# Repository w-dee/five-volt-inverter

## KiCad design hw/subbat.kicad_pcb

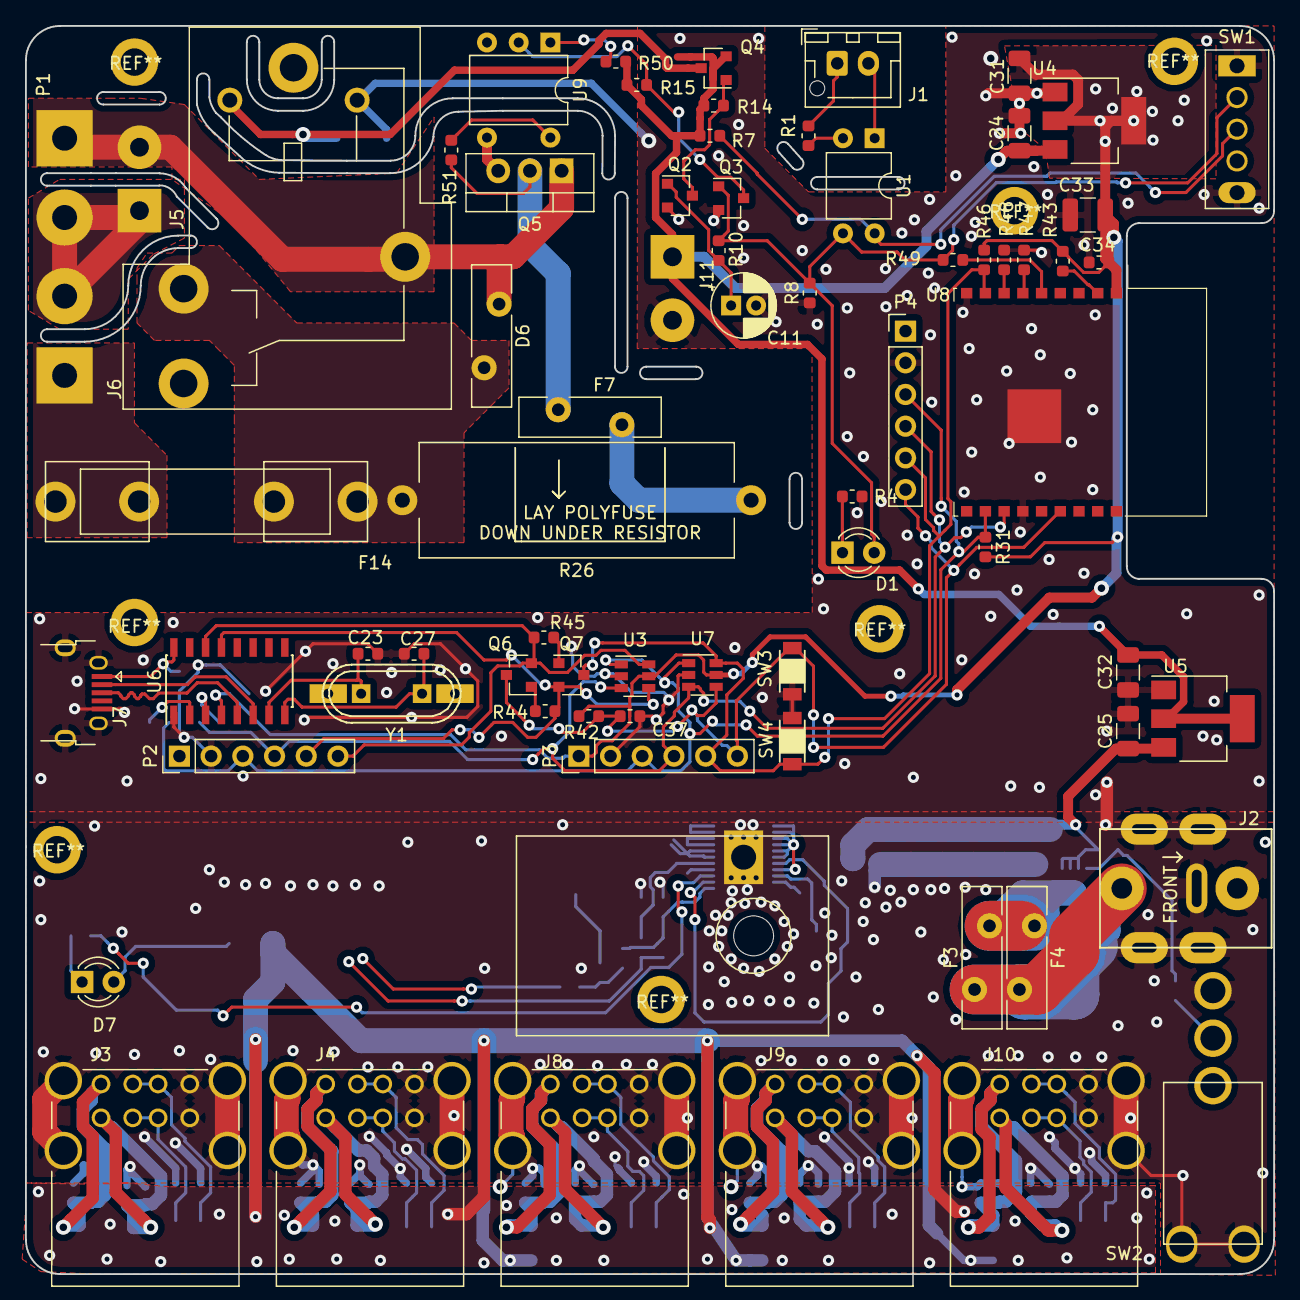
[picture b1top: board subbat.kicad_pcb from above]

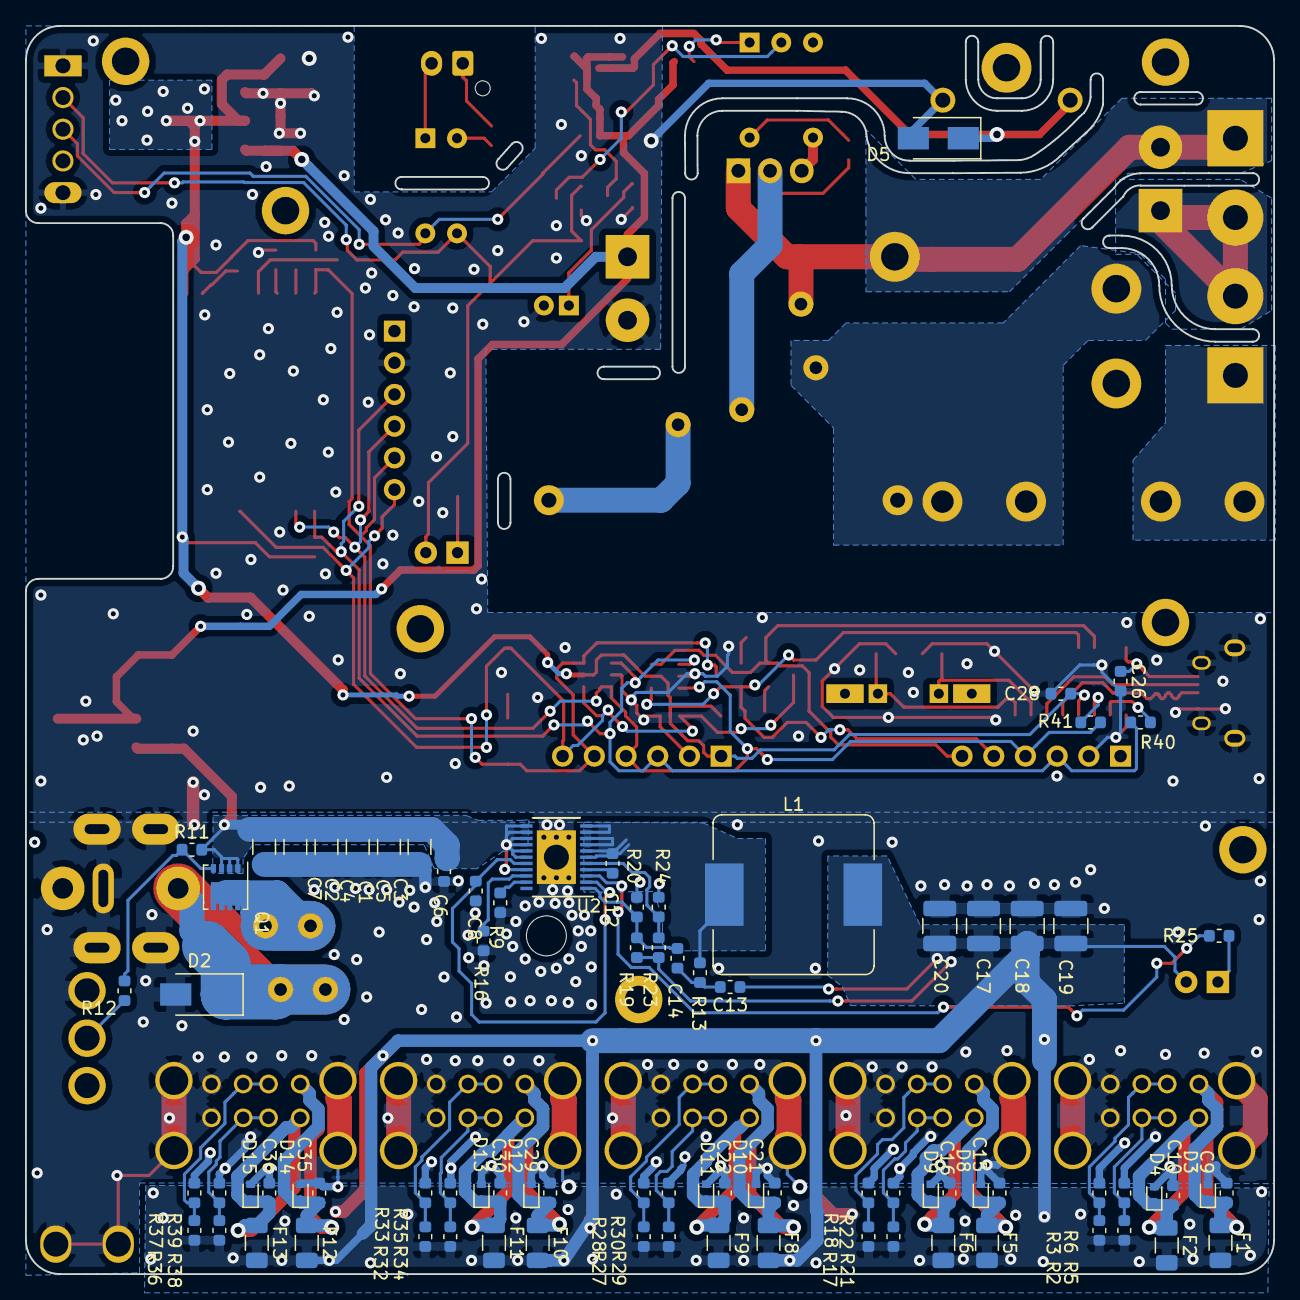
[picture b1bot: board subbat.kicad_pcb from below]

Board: 2 copper layers, 100.0 x 100.0 mm, 155 parts (84 on the bottom side), 77 nets.

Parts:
C1, C2, C3, C4, C5, C7, C24, C25, C31, C32: 10u; C_1206_3216Metric
C6, C8, C9, C10, C15, C16, C21, C22, C26, C28, C29, C30, C34, C35, C36: 1u; C_0603_1608Metric
C11: 22u; CP_Radial_D5.0mm_P2.00mm
C12, C13, C37: 0.1u; C_0603_1608Metric
C14: 1n; C_0603_1608Metric
C17, C18, C19, C20, C33: 100u/6.3V; C_1210_3225Metric
C23, C27: 22p; C_0603_1608Metric
D1, D7: LED; LED_D3.0mm
D2: 28V TVS; D_SMA
D3, D4, D8, D9, D10, D11, D12, D13, D14, D15: 6V; D_SOD-523
D5: D_Schottky_Small; D_SMA
D6: TSV07D271KR; Fuse_Bourns_MF-RG700
F1, F2, F5, F6, F8, F9, F10, F11, F12, F13: 2A; Fuse_1206_3216Metric
F3, F4: 3A hold; Fuse_Bourns_MF-RG700
F7: LVR040S 0.4A hold, 0.9A trip; Fuse_Bourns_MF-RHT600
F14: 15A; FUSE-HOLDER-FUC-03A-20mm_x_5.2mm
J1: Conn_01x02_Female; JST_XH_B02B-XH-AM_1x02_P2.50mm_Vertical
J2: Barrel_Jack; BARREL_JACK_HIGH_CURRENT_PJ018
J3, J4, J8, J9, J10: USB_Ax2
J5, J11: Conn_01x02_Female; SolderWirePad_1x02_P5.08mm_Drill1.5mm
J6: Conn_WallSocket; SolderWirePad_1x02_P7.62mm_Drill2mm
J7: USB_B_Micro; USB_Micro-B_Jing_A01SB141B1-067
K1: 953-1C-5DG-1
L1: 1.5uH 29A; L_Bourns_SRP1245A
P1: Conn_WallPlug; SolderWirePad_1x02_P7.62mm_Drill2mm
P2, P3, P4: CONN_01X06; PinHeader_1x06_P2.54mm_Vertical
Q1: DMP3007SCG; Diodes_PowerDI3333-8
Q2, Q3: 2N7002; SOT-23
Q4: Q_PMOS_GSD; SOT-23
Q5: BTA24-600CW; TO-220-3_Vertical
Q6, Q7: Q_NPN_BEC; SOT-23
R1, R49, R51: 100R; R_0603_1608Metric
R2, R3, R5, R6, R17, R18, R21, R22, R27, R28, R29, R30, R32, R33, R34, R35, R36, R37, R38, R39: DNI; R_0603_1608Metric
R4: 2.2k; R_0603_1608Metric
R7: 10R; R_0603_1608Metric
R8, R15, R20, R24, R31, R43, R44, R45, R47, R48: 10k; R_0603_1608Metric
R9: 150k; R_0603_1608Metric
R10: 22k; R_0603_1608Metric
R11: 1M; R_0603_1608Metric
R12: 22K; R_0603_1608Metric
R13: 3k; R_0603_1608Metric
R14, R42, R46: 100k; R_0603_1608Metric
R16: 200k; R_0603_1608Metric
R19, R23: 75k; R_0603_1608Metric
R25: 1k; R_0603_1608Metric
R26: 100R; R_Axial_Power_L25.0mm_W9.0mm_P27.94mm
R40, R41: 120R; R_0603_1608Metric
R50: 330R; R_0603_1608Metric
SW1: SW_SPDT_WITH_SHIELD; SW_SPDT_WITH_SHILD
SW2: SW_SPDT_WITH_SHIELD; SW_SPDT_v
SW3, SW4: SW_PUSH_SMALL_H; TACT_SW_SMD_Panasonic-EVPAWBD2A
U1: PC817; DIP-4_W7.62mm
U2: TPS53319; DFN-22-1EP_5x6mm_P0.5mm_EP3.14x4.3mm
U3, U7: CM1293A-04SO; SOT-23-6
U4: AZ1117-3.3; SOT-223-3_TabPin2
U5: AZ1117-5.0; SOT-223-3_TabPin2
U6: CH340G; SOIC-16_3.9x9.9mm_P1.27mm
U8: ESP-WROOM-02
U9: TLP561J; Toshiba_11-7A9
Y1: Crystal; Crystal_HC49-U_Vertical_SMD_Universal

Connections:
+3V3: C28.1, C31.1, C33.1, C34.1, P3.1, R31.2, R42.1, R43.1, R46.1, U3.5, U4.2, U6.4, U7.5, U8.1
+5V: C24.1, C32.1, J11.1, Q4.2, R7.2, R14.1, R15.1, R50.2, U4.3, U5.2
/AC_IN_L: D6.1, J5.2, K1.5, P1.1, Q5.1
/AC_IN_N: J5.1, J6.2, P1.2
/AC_OUT_L: D6.2, F14.1, K1.1, R26.2
/AC_OUT_L_2: F14.2, J6.1
/LL: C12.2, L1.1, R13.1, U2.6, U2.7, U2.8, U2.9, U2.10, U2.11
/SW: D1.2, Q3.1, R8.2, R10.2, R49.2, SW1.1, U1.3
/VIN: C1.1, C2.1, C3.1, C4.1, C5.1, C6.1, C7.1, C25.1, Q1.1, Q1.2, Q1.3, R11.2, U2.12, U2.13, U2.14, U2.15, U2.16, U2.17, U2.19, U5.3
DTR: P2.5, Q7.2, R44.2, U3.4, U6.13
E_EN: C37.2, P3.6, P4.6, Q6.3, R42.2, SW3.1, U7.4, U8.15
E_GPIO0: P3.5, P4.5, Q7.3, R46.2, SW4.2, U7.6, U8.8
E_RX: P2.3, P3.3, P4.3, R31.1, R40.2, U3.1, U7.1, U8.11
E_TX: P2.4, P3.4, P4.4, R41.2, U3.3, U7.3, U8.12
GND: C1.2, C2.2, C3.2, C4.2, C5.2, C6.2, C7.2, C8.2, C9.2, C10.2, C11.2, C15.2, C16.2, C17.2, C18.2, C19.2, C20.2, C21.2, C22.2, C23.2, C24.2, C25.2, C26.2, C27.2, C28.2, C29.2, C30.2, C31.2, C32.2, C33.2, C34.2, C35.2, C36.2, C37.1, D2.2, D3.2, D4.2, D5.2, D8.2, D9.2, D10.2, D11.2, D12.2, D13.2, D14.2, D15.2, J2.2, J2.3, J3.4, J3.8, J3.9, J4.4, J4.8, J4.9, J7.5, J7.6, J8.4, J8.8, J8.9, J9.4, J9.8, J9.9, J10.4, J10.8, J10.9, J11.2, K1.3, P2.2, P3.2, P4.2, Q2.2, Q3.2, R3.2, R4.1, R6.2, R8.1, R9.1, R16.2, R18.2, R20.2, R22.2, R24.2, R28.2, R30.2, R33.2, R35.2, R37.2, R39.2, R47.2, R48.2, SW1.4, SW1.5, SW2.3, SW2.4, SW2.5, SW3.2, SW4.1, U2.23, U3.2, U4.1, U5.1, U6.1, U7.2, U8.9, U8.13, U8.18, U8.19
unnamed: C8.1, U2.2, U2.18
unnamed: C9.1, D3.1, F1.1, J3.1
unnamed: C10.1, D4.1, F2.1, J3.5
unnamed: C11.1, Q2.1, R10.1
unnamed: C12.1, U2.4
unnamed: C13.2, C14.2, R13.2
unnamed: C14.1, R19.2, R20.1, U2.1
unnamed: C15.1, D8.1, F5.1, J4.1
unnamed: C16.1, D9.1, F6.1, J4.5
unnamed: C21.1, D10.1, F8.1, J8.1
unnamed: C22.1, D11.1, F9.1, J8.5
unnamed: C23.1, U6.7, Y1.1
unnamed: C26.1, J7.1, U6.16
unnamed: C27.1, U6.8, Y1.2
unnamed: C29.1, D12.1, F10.1, J9.1
unnamed: C30.1, D13.1, F11.1, J9.5
unnamed: C35.1, D14.1, F12.1, J10.1
unnamed: C36.1, D15.1, F13.1, J10.5
unnamed: D1.1, R4.2
unnamed: D2.1, F3.1, F4.2, J2.1
unnamed: D5.1, K1.4, Q4.3
unnamed: D7.1, R25.1
unnamed: F3.2, F4.1, Q1.5
unnamed: F7.1, R26.1
unnamed: F7.2, Q5.2, R51.2
unnamed: J1.1, R1.1
unnamed: J1.2, U1.1
unnamed: J3.2, J3.3, R2.2, R3.1
unnamed: J3.6, J3.7, R5.2, R6.1
unnamed: J4.2, J4.3, R17.2, R18.1
unnamed: J4.6, J4.7, R21.2, R22.1
unnamed: J7.2, U6.6
unnamed: J7.3, U6.5
unnamed: J8.2, J8.3, R27.2, R28.1
unnamed: J8.6, J8.7, R29.2, R30.1
unnamed: J9.2, J9.3, R32.2, R33.1
unnamed: J9.6, J9.7, R34.2, R35.1
unnamed: J10.2, J10.3, R36.2, R37.1
unnamed: J10.6, J10.7, R38.2, R39.1
unnamed: Q1.4, R11.1, R12.2
unnamed: Q2.3, Q4.1, R14.2
unnamed: Q3.3, R15.2, U9.2
unnamed: Q5.3, U9.4
unnamed: Q6.1, R44.1
unnamed: Q7.1, R45.1
unnamed: R1.2, U1.2
unnamed: R7.1, SW1.2, U1.4
unnamed: R9.2, U2.21
unnamed: R12.1, SW2.2
unnamed: R16.1, U2.20
unnamed: R23.2, R24.1, U2.5
unnamed: R25.2, U2.3
unnamed: R40.1, U6.2
unnamed: R41.1, U6.3
unnamed: R43.2, U8.2
unnamed: R47.1, U8.6
unnamed: R48.1, U8.7
unnamed: R49.1, U8.5
unnamed: R50.1, U9.1
unnamed: R51.1, U9.6
RTS: P2.6, Q6.2, R45.2, U3.6, U6.14
VCOM: C13.1, C17.1, C18.1, C19.1, C20.1, D7.2, F1.2, F2.2, F5.2, F6.2, F8.2, F9.2, F10.2, F11.2, F12.2, F13.2, L1.2, R2.1, R5.1, R17.1, R19.1, R21.1, R23.1, R27.1, R29.1, R32.1, R34.1, R36.1, R38.1

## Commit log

2018-12-12 Added a spark killer
2018-12-15 To make easy chassis making
